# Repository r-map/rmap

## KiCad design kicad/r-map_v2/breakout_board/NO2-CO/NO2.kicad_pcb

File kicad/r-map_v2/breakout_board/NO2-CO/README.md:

Schematic preview
=================

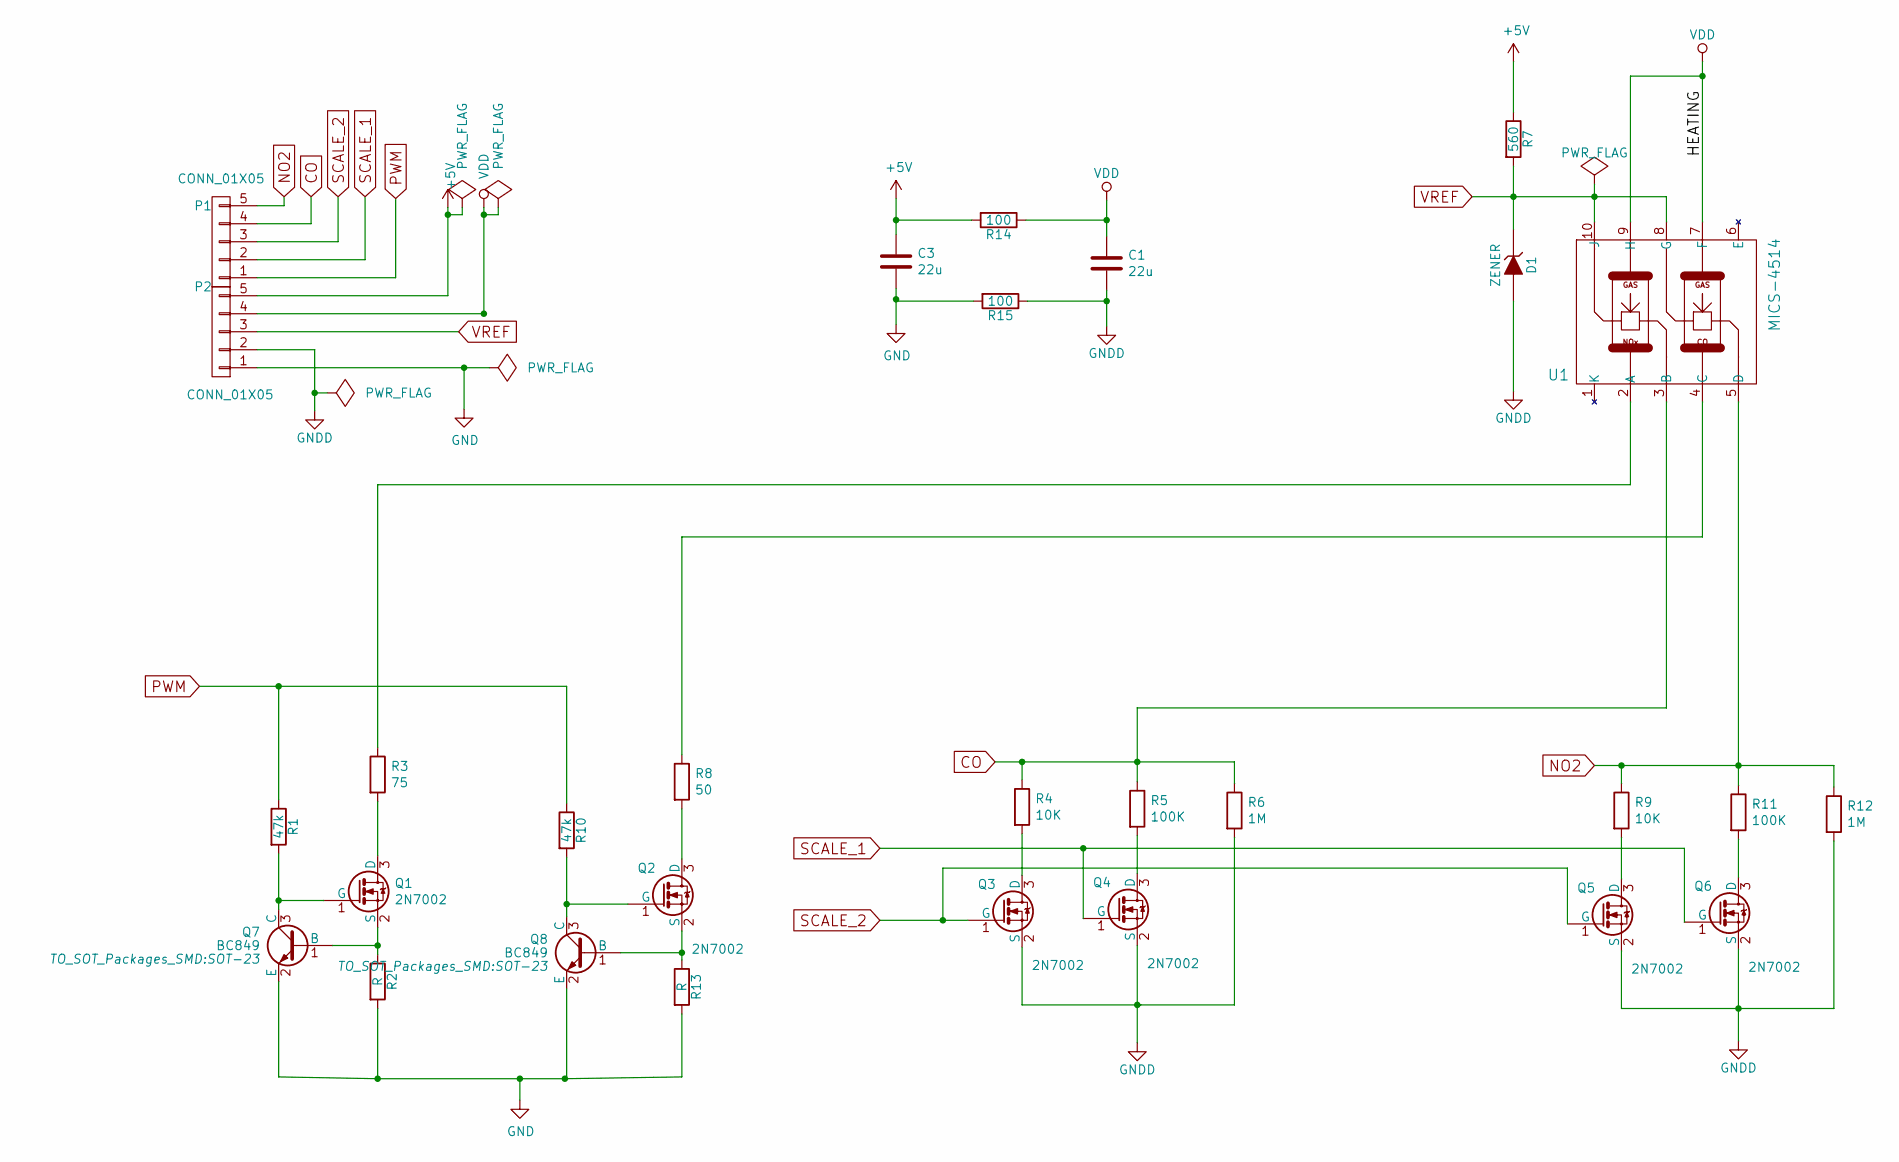
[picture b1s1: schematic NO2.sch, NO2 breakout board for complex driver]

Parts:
C1, C3: 22u; C_0805_HandSoldering
D1: ZENER; SOT-23
P1, P2: CONN_01X05; Pin_Header_Straight_1x05_Pitch2.54mm
Q1, Q2, Q3, Q4, Q5, Q6: 2N7002; SOT-23
Q7, Q8: BC849; SOT-23
R1, R10: 47k; R_0805_HandSoldering
R2, R13: R; R_0805_HandSoldering
R3: 75; R_0805_HandSoldering
R4, R9: 10K; R_0805_HandSoldering
R5, R11: 100K; R_0805_HandSoldering
R6, R12: 1M; R_0805_HandSoldering
R7: 560; R_0805_HandSoldering
R8: 50; R_0805_HandSoldering
R14, R15: 100; R_0805_HandSoldering
U1: MICS-4514

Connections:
+5V: C3.1, P2.5, R7.1, R14.2
CO: P1.4, R4.1, R5.1, R6.1, U1.3 (B)
GND: C3.2, P2.1, Q7.2 (E), Q8.2 (E), R2.2, R13.2, R15.2
GNDD: C1.2, D1.2 (A), P2.2, Q3.2 (S), Q4.2 (S), Q5.2 (S), Q6.2 (S), R6.2, R12.2, R15.1
NO2: P1.5, R9.1, R11.1, R12.1, U1.5 (D)
unnamed: Q1.1 (G), Q7.3 (C), R1.2
unnamed: Q1.2 (S), Q7.1 (B), R2.1
unnamed: Q1.3 (D), R3.2
unnamed: Q2.1 (G), Q8.3 (C), R10.2
unnamed: Q2.2 (S), Q8.1 (B), R13.1
unnamed: Q2.3 (D), R8.2
unnamed: Q3.3 (D), R4.2
unnamed: Q4.3 (D), R5.2
unnamed: Q5.3 (D), R9.2
unnamed: Q6.3 (D), R11.2
unnamed: R3.1, U1.2 (A)
unnamed: R8.1, U1.4 (C)
PWM: P1.1, R1.1, R10.1
SCALE_1: P1.2, Q4.1 (G), Q6.1 (G)
SCALE_2: P1.3, Q3.1 (G), Q5.1 (G)
VDD: C1.1, P2.4, R14.1, U1.7 (F), U1.9 (H)
VREF: D1.1 (K), P2.3, R7.2, U1.8 (G), U1.10 (J)

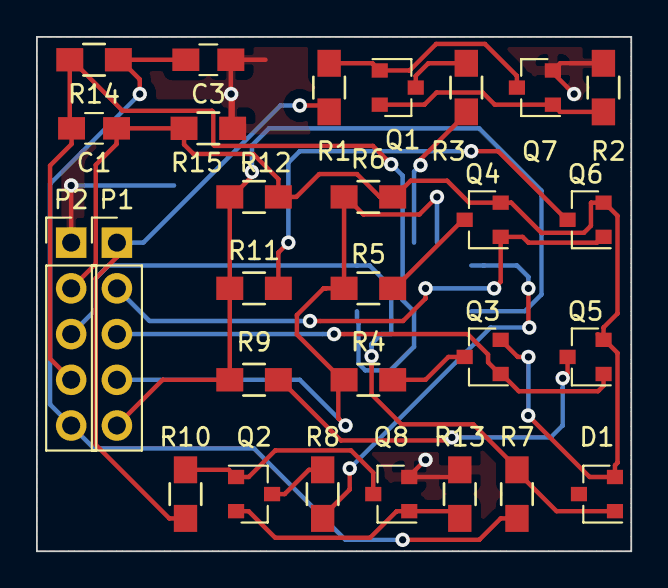
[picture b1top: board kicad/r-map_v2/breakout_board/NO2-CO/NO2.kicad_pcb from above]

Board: 2 copper layers, 33.0 x 28.6 mm, 29 parts (1 on the bottom side), 22 nets.

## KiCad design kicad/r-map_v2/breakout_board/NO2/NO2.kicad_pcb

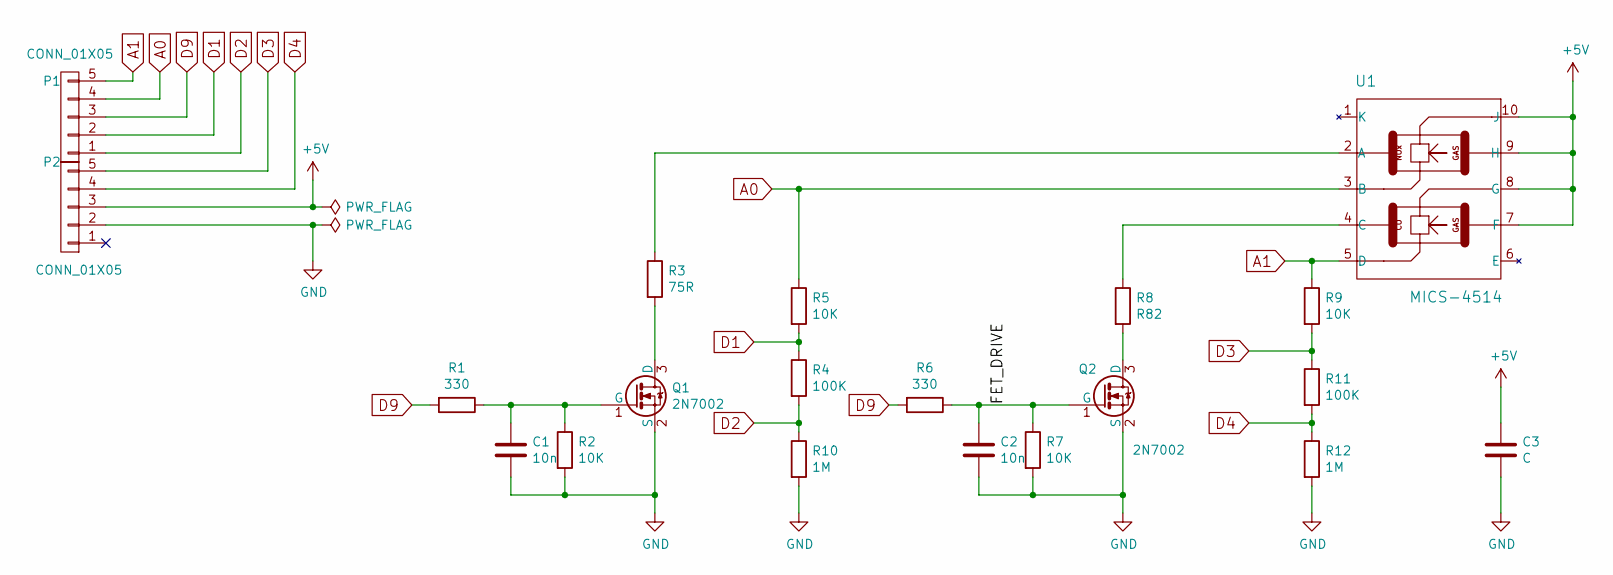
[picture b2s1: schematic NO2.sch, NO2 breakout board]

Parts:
C1, C2: 10n; C_0805_HandSoldering
C3: C
P1, P2: CONN_01X05
Q1, Q2: 2N7002; SOT-23
R1, R6: 330; R_0805
R2, R5, R7, R9: 10K; R_0805
R3: 75R; R_0805
R4, R11: 100K
R8: R82; R_0805
R10, R12: 1M
U1: MICS-4514

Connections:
+5V: C3.1, P2.3, U1.7 (F), U1.8 (G), U1.9 (H), U1.10 (J)
/FET_DRIVE: C2.1, Q2.1 (G), R6.1, R7.1
A0: P1.4, R5.1, U1.3 (B)
A1: P1.5, R9.1, U1.5 (D)
D1: P1.2, R4.1, R5.2
D2: P1.1, R4.2, R10.1
D3: P2.5, R9.2, R11.1
D4: P2.4, R11.2, R12.1
D9: P1.3, R1.2, R6.2
GND: C1.2, C2.2, C3.2, P2.2, Q1.2 (S), Q2.2 (S), R2.2, R7.2, R10.2, R12.2
unnamed: C1.1, Q1.1 (G), R1.1, R2.1
unnamed: Q1.3 (D), R3.2
unnamed: Q2.3 (D), R8.2
unnamed: R3.1, U1.2 (A)
unnamed: R8.1, U1.4 (C)

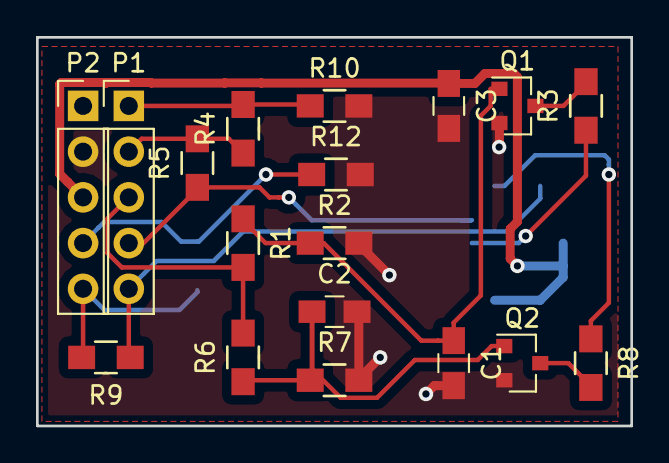
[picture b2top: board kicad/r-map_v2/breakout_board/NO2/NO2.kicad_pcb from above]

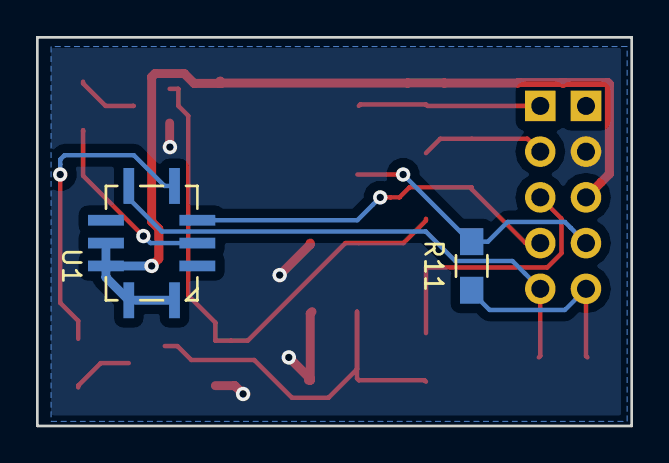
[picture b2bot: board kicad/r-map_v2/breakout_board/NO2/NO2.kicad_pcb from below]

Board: 2 copper layers, 33.0 x 21.6 mm, 20 parts (2 on the bottom side), 15 nets.

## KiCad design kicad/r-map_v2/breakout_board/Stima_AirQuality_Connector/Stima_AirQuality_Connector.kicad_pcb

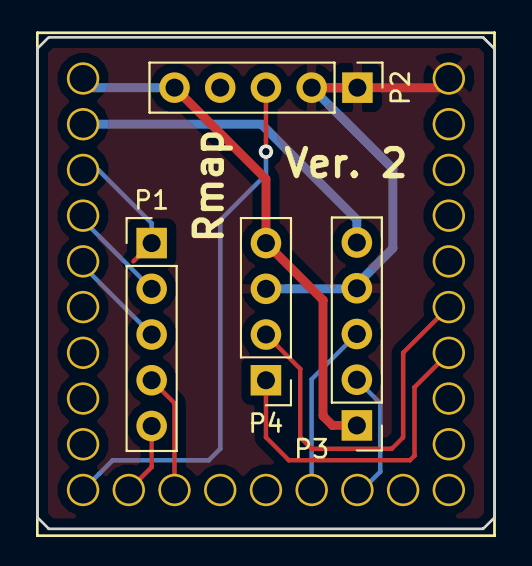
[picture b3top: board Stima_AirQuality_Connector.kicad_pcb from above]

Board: 2 copper layers, 25.4 x 27.3 mm, 5 parts (0 on the bottom side), 13 nets.

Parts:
P1, P2, P3: CONN_01X05; Pin_Header_Straight_1x05_Pitch2.54mm
P4: CONN_01X04; Pin_Header_Straight_1x04_Pitch2.54mm
U1: Microduino; microduino

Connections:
+3V3: P3.5, U1.26
+5V: P2.5, P3.1, P4.4, U1.27
CO: P1.4, U1.16
GND: P2.1, P2.2, P3.4, P4.3, U1.1
NO2: P1.5, U1.17
PWM: P1.1, U1.25
RX: P4.1, U1.7
SCALE_1: P1.2, U1.24
SCALE_2: P1.3, U1.23
SCL: P3.2, U1.12
SDA: P3.3, U1.13
TX: P4.2, U1.6
VREF: P2.3, U1.18

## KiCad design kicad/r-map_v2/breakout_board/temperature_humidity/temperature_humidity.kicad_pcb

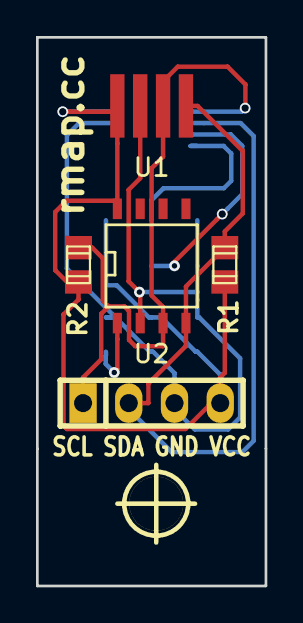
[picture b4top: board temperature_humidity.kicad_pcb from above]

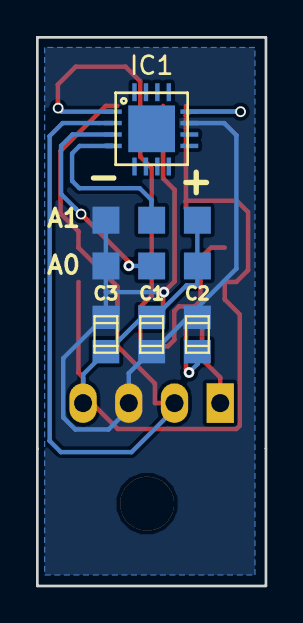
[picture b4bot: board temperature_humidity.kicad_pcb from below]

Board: 2 copper layers, 12.7 x 30.5 mm, 16 parts (8 on the bottom side), 7 nets.

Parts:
3.3V1, 3.3V2: 3.3V; Measurement_Point_Square-SMD-Pad_Small
A1: A1; Measurement_Point_Square-SMD-Pad_Small
C1: 0.22uF; c_0805
C2, C3: 0.1uF; c_0805
GND1, GND3: GND; Measurement_Point_Square-SMD-Pad_Small
IC1: ADT7420; LFCSP_WQ_CP16-17
P3: CONN_01X04; pin_strip_4
P4: A0; Measurement_Point_Square-SMD-Pad_Small
R1, R2: R; r_0805
U1: HIH6100; SIP4_ANGLED
U2: HIH6100-SOIC8; SOIC-8-N
hole_3mm: VAL**; hole_3mm

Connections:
+3.3V: 3.3V1.1, 3.3V2.1, C1.1, C3.1, IC1.12, P3.4, R1.1, R2.1, U1.1, U2.8
/A0: IC1.3, P4.1
/A1: A1.1, IC1.4
GND: C1.2, C2.2, C3.2, GND1.1, GND3.1, IC1.11, P3.3, U1.2, U2.2
unnamed: C2.1, U2.1
SCL: IC1.1, P3.1, R2.2, U1.3, U2.3
SDA: IC1.2, P3.2, R1.2, U1.4, U2.4

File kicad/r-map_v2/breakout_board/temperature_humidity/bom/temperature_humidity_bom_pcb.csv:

Item,Reference(s),Value,Quantity,
1,3.3V1 3.3V2,3.3V,2,Piazzola no componenti
2,A1,A1,1,Piazzola no componenti
3,C1,0.22uF,1,http://it.farnell.com/multicomp/mc0805b224m250ct/ceramic-cap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
4,C2 C3,0.1uF,3,http://it.farnell.com/avx/08053e104zat2a/ceramic-capacitor-0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
5,GND1 GND3,GND,2,Piazzola no componenti
6,IC1,ADT7420,1,http://it.farnell.com/analog-devices/adt7420ucpz-r2/temp-sen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
7,P3,CONN_01X04,1,http://it.farnell.com/multicomp/2211s-04g/connettore-header-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
8,P4,A0,1,Piazzola no componenti
9,U1,HIH6100,1,Honeywell HIH6100
10,U2,HIH6100-SOIC8,1,Honeywell HIH6100-SOIC8

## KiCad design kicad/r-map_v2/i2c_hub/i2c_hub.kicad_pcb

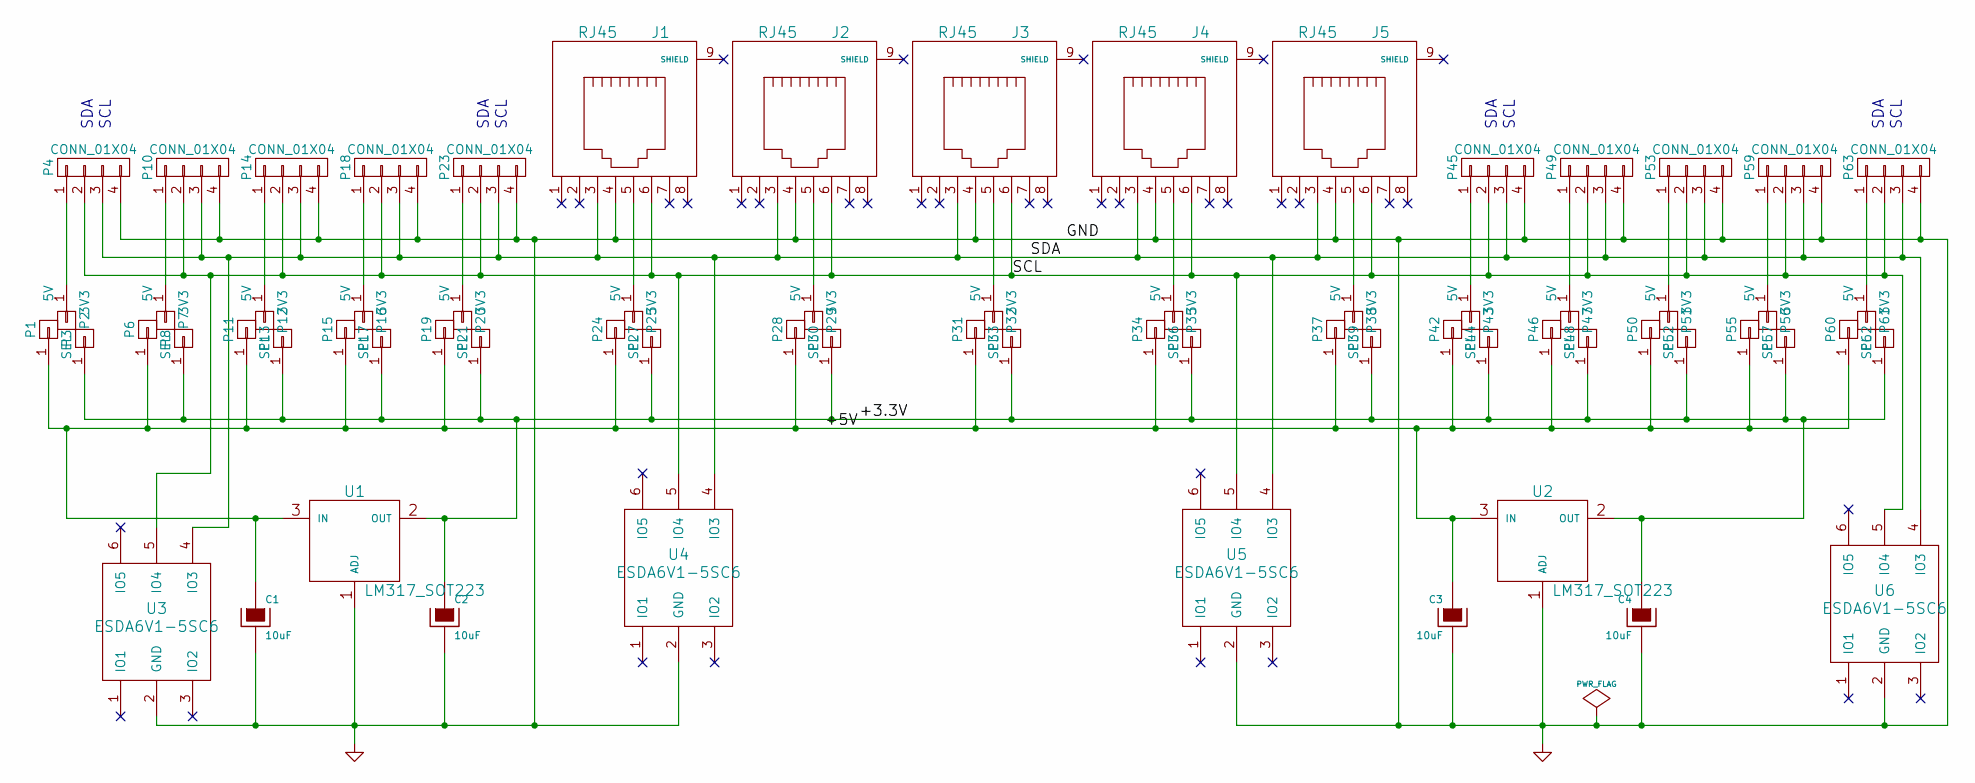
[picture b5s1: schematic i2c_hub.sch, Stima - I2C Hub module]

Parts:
C1, C2, C3, C4: 10uF; c_1206
J1, J2, J3, J4, J5: RJ45; RJ45_8
P1, P6, P11, P15, P19, P24, P28, P31, P34, P37, P42, P46, P50, P55, P60: 5V; Measurement_Point_Round-SMD-Pad_Small
P2, P7, P12, P16, P20, P25, P29, P32, P35, P38, P43, P47, P51, P56, P61: SEL; Measurement_Point_Round-SMD-Pad_Small
P3, P8, P13, P17, P21, P27, P30, P33, P36, P39, P44, P48, P52, P57, P62: 3V3; Measurement_Point_Round-SMD-Pad_Small
P4, P10, P14, P18, P23, P45, P49, P53, P59, P63: CONN_01X04; pin_strip_4
U1, U2: LM317_SOT223; sot223
U3, U4, U5, U6: ESDA6V1-5SC6; sot23-6

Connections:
/+3.3V: C2.1, C4.1, P3.1, P8.1, P13.1, P17.1, P21.1, P27.1, P30.1, P33.1, P36.1, P39.1, P44.1, P48.1, P52.1, P57.1, P62.1, U1.2 (OUT), U2.2 (OUT), U3.1 (IO1), U5.1 (IO1), U6.1 (IO1)
/+5V: C1.1, C3.1, P1.1, P6.1, P11.1, P15.1, P19.1, P24.1, P28.1, P31.1, P34.1, P37.1, P42.1, P46.1, P50.1, P55.1, P60.1, U1.3 (IN), U2.3 (IN), U3.6 (IO5), U4.1 (IO1), U4.6 (IO5), U5.6 (IO5), U6.6 (IO5)
/SCL: J1.6, J2.6, J3.6, J4.6, J5.6, P4.2, P10.2, P14.2, P18.2, P23.2, P45.2, P49.2, P53.2, P59.2, P63.2, U3.5 (IO4), U4.5 (IO4), U5.5 (IO4), U6.5 (IO4)
/SDA: J1.3, J2.3, J3.3, J4.3, J5.3, P4.3, P10.3, P14.3, P18.3, P23.3, P45.3, P49.3, P53.3, P59.3, P63.3, U3.4 (IO3), U4.4 (IO3), U5.4 (IO3), U6.4 (IO3)
GND: C1.2, C2.2, C3.2, C4.2, J1.4, J2.4, J3.4, J4.4, J5.4, P4.4, P10.4, P14.4, P18.4, P23.4, P45.4, P49.4, P53.4, P59.4, P63.4, U1.1 (ADJ), U2.1 (ADJ), U3.2 (GND), U4.2 (GND), U5.2 (GND), U6.2 (GND)
unnamed: J1.5, P25.1
unnamed: J2.5, P29.1
unnamed: J3.5, P32.1
unnamed: J4.5, P35.1
unnamed: J5.5, P38.1
unnamed: P2.1, P4.1
unnamed: P7.1, P10.1
unnamed: P12.1, P14.1
unnamed: P16.1, P18.1
unnamed: P20.1, P23.1
unnamed: P43.1, P45.1
unnamed: P47.1, P49.1
unnamed: P51.1, P53.1
unnamed: P56.1, P59.1
unnamed: P61.1, P63.1

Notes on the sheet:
SDA
SCL

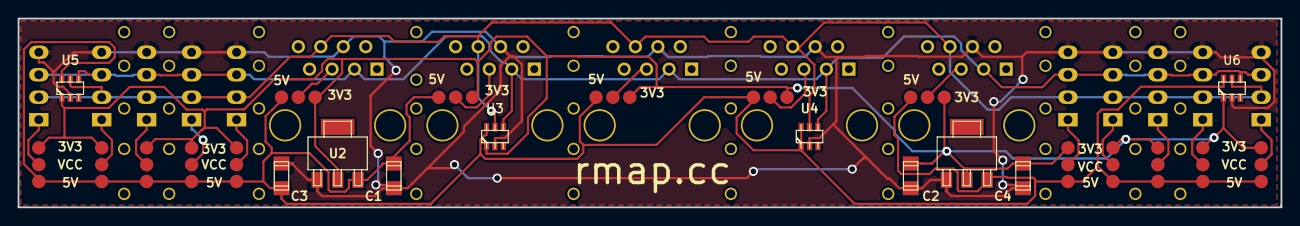
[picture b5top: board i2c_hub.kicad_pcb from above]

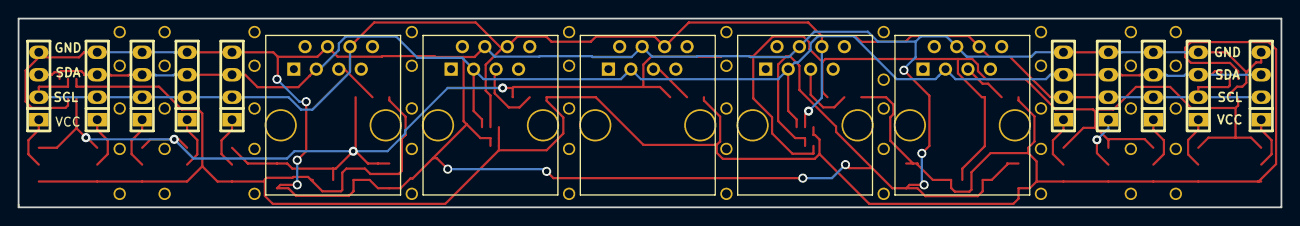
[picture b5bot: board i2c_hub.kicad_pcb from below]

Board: 2 copper layers, 142.7 x 21.3 mm, 70 parts (15 on the bottom side), 20 nets.

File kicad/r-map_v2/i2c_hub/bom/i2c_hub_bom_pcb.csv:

Item,Reference(s),Value,Quantity,Package,Esempio
1,C1 C2 C3 C4,10uF,4,1206 smd,http://it.farnell.com/kemet/c1206c106k4pactu/condensatore-ml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
2,J1 J2 J3 J4 J5,RJ45,5,connettore RJ45 non schermato, http://it.farnell.com/fci/54601-908wplf/modulare-jack-tht-r-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
3,P1 P11 P15 P19 P24 P28 P31 P34 P37 P42 P46 P50 P55 P6 P60,5V,15,piazzola senza componenti,
4,P10 P14 P18 P23 P4 P45 P49 P53 P59 P63,CONN_01X04,10,strip connector maschio 4 pin,
5,P12 P16 P2 P20 P25 P29 P32 P35 P38 P43 P47 P51 P56 P61 P7,SEL,15,piazzola senza componenti,
6,P13 P17 P21 P27 P3 P30 P33 P36 P39 P44 P48 P52 P57 P62 P8,3V3,15,piazzola senza componenti,
7,U1 U2,LM1117-3.3,2,SOT-223 smd,http://it.farnell.com/texas-instruments/lm1117mp-3-3/v-reg-l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
8,U3 U4 U5 U6,ESDA6V1-5SC6,4,SOT23-6 smd,http://it.farnell.com/stmicroelectronics/esda6v1-5sc6/transi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

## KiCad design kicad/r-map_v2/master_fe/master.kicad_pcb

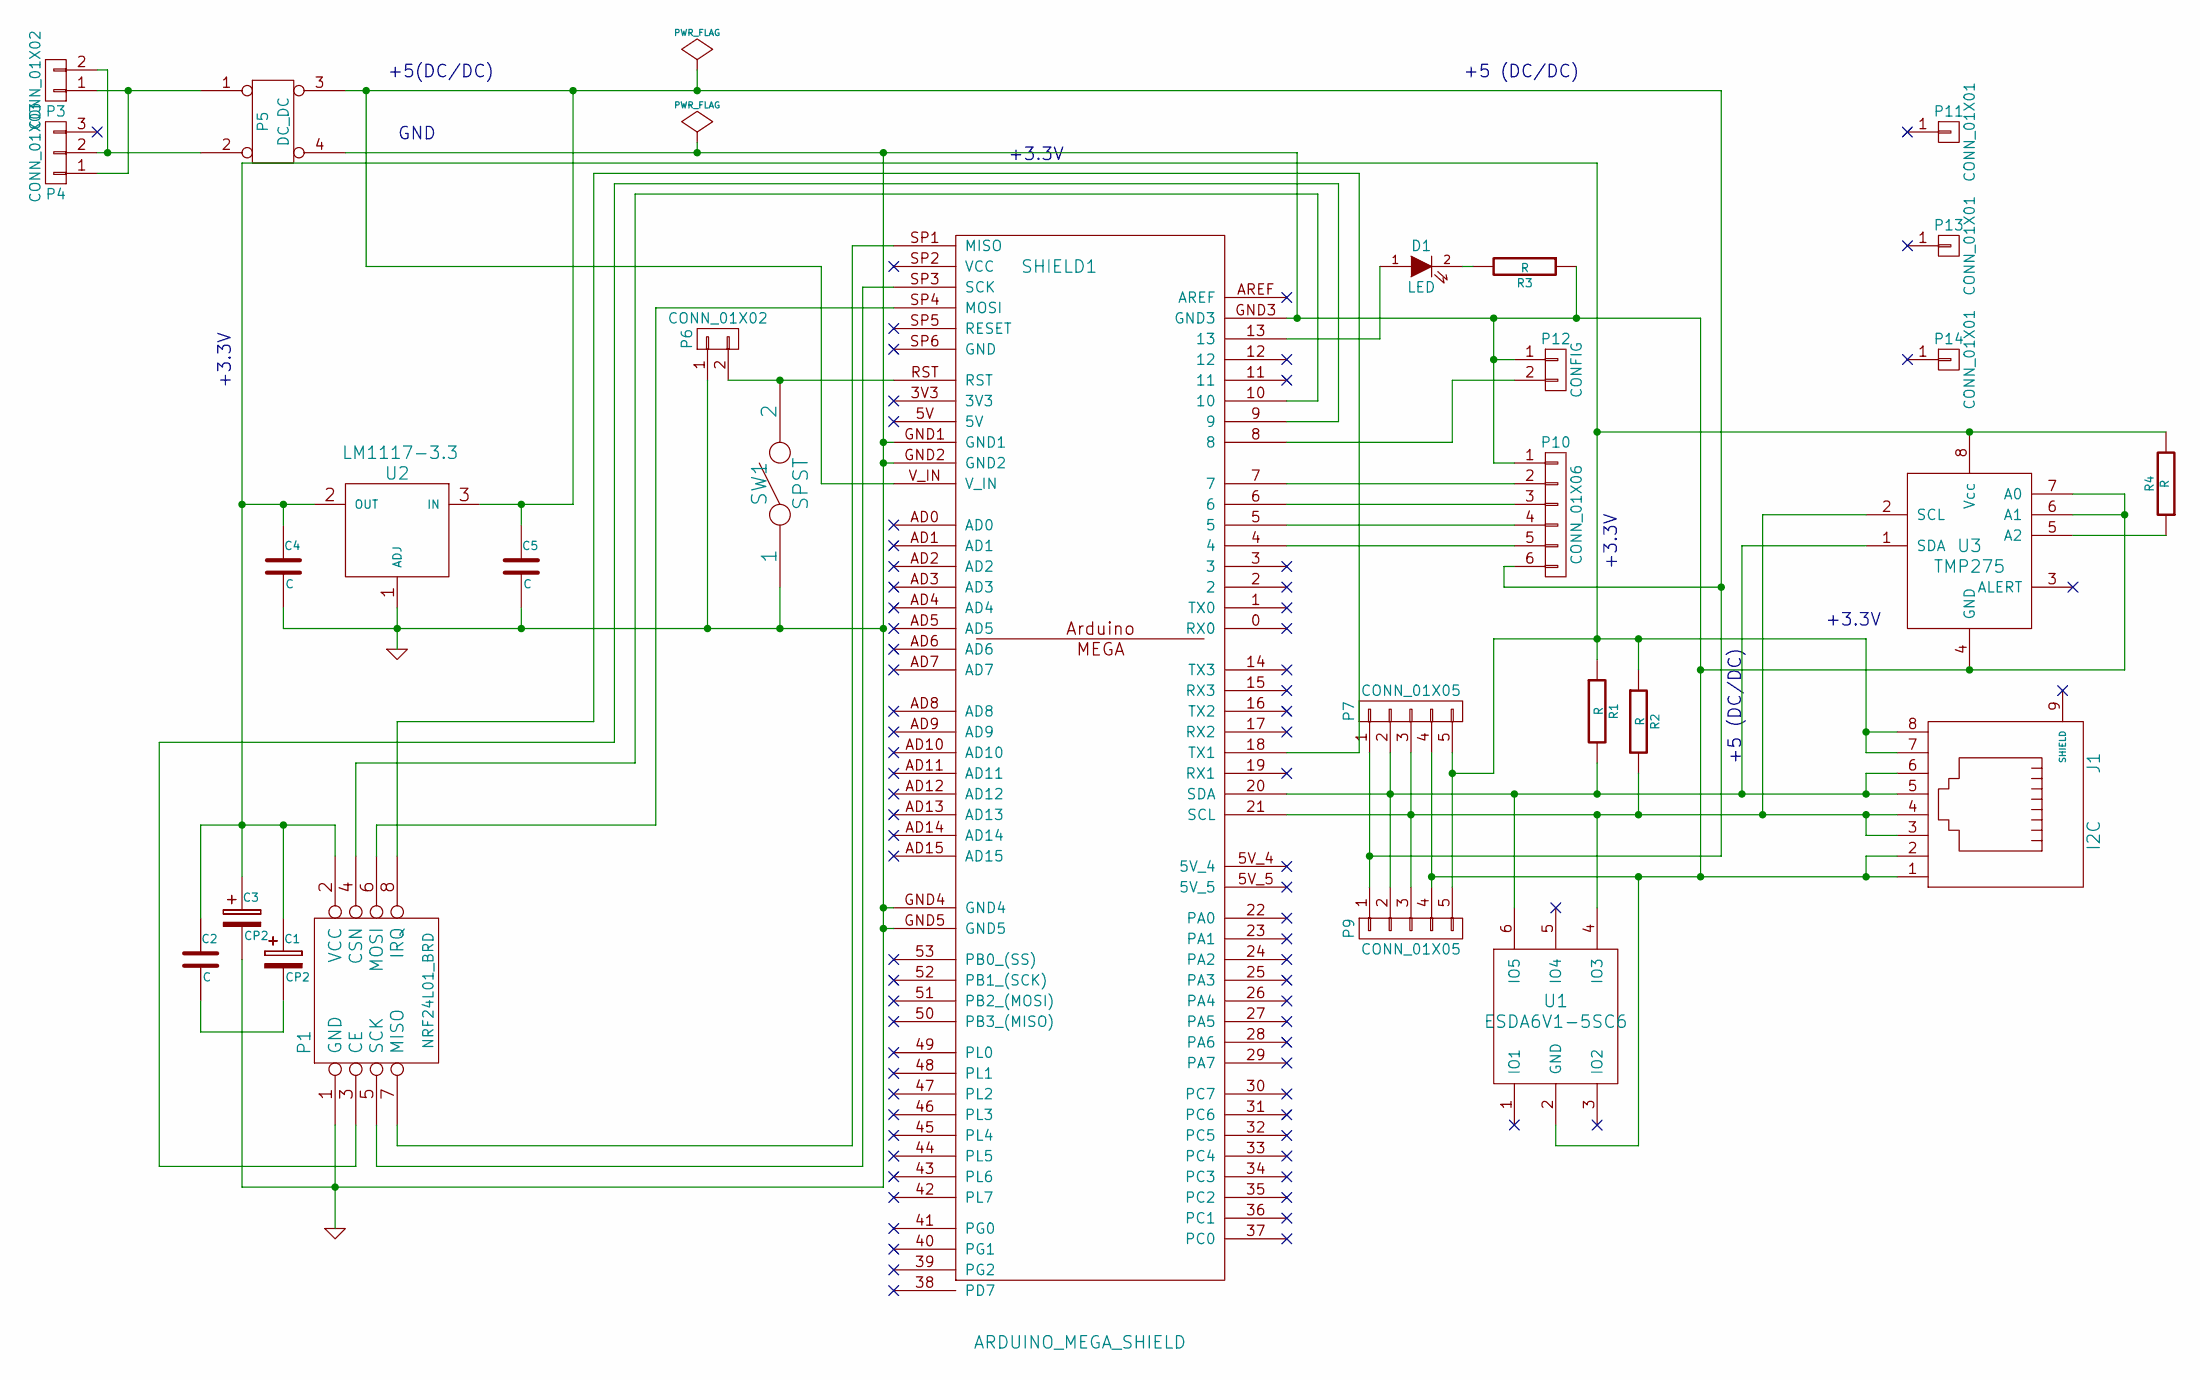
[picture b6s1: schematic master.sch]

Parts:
C1: CP2; SMD-1206
C2, C4, C5: C; SMD-1206
C3: CP2; C1.5V8V
D1: LED; LED-3MM
J1: I2C; RJ45_8
P1: NRF24L01_BRD; NRF24L01
P3, P6: CONN_01X02; Pin_Header_Straight_1x02
P4: CONN_01X03; BARREL_JACK
P5: DC_DC
P7, P9: CONN_01X05; Pin_Header_Straight_1x05
P10: CONN_01X06; Pin_Header_Straight_1x06
P11, P13, P14: CONN_01X01; MountingHole_3mm
P12: CONFIG; Pin_Header_Straight_1x02
R1, R2, R3, R4: R; R3-LARGE_PADS
SHIELD1: ARDUINO_MEGA_SHIELD
SW1: SPST; SW_PUSH_SMALL
U1: ESDA6V1-5SC6; SOT-23-6
U2: LM1117-3.3; SOT-223
U3: TMP275; SO-8

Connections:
GND: C3.2, C4.2, C5.2, J1.1, J1.2, P1.1 (GND), P5.4, P6.1, P7.4, P9.4, P10.1, P12.1, R3.1, SHIELD1.GND1, SHIELD1.GND2, SHIELD1.GND3, SHIELD1.GND4, SHIELD1.GND5, SW1.1, U1.2 (GND), U2.1 (ADJ), U3.4 (GND), U3.6 (A1), U3.7 (A0)
unnamed: C1.1, C2.1, C3.1, C4.1, J1.7, J1.8, P1.2 (VCC), P7.5, P9.5, R1.1, R2.1, R4.2, U2.2 (OUT), U3.8 (Vcc)
unnamed: C1.2, C2.2
unnamed: C5.1, P5.3, P7.1, P9.1, P10.6, SHIELD1.V_IN, U2.3 (IN)
unnamed: D1.1 (A), SHIELD1.13
unnamed: D1.2 (K), R3.2
unnamed: J1.3, J1.4, P7.3, P9.3, R2.2, SHIELD1.21 (SCL), U1.4 (IO3), U3.2 (SCL)
unnamed: J1.5, J1.6, P7.2, P9.2, R1.2, SHIELD1.20 (SDA), U1.6 (IO5), U3.1 (SDA)
unnamed: P1.3 (CE), SHIELD1.9
unnamed: P1.4 (CSN), SHIELD1.10
unnamed: P1.5 (SCK), SHIELD1.SP3 (SCK)
unnamed: P1.6 (MOSI), SHIELD1.SP4 (MOSI)
unnamed: P1.7 (MISO), SHIELD1.SP1 (MISO)
unnamed: P1.8 (IRQ), SHIELD1.18 (TX1)
unnamed: P3.1, P4.1, P5.1
unnamed: P3.2, P4.2, P5.2
unnamed: P6.2, SHIELD1.RST, SW1.2
unnamed: P10.2, SHIELD1.7
unnamed: P10.3, SHIELD1.6
unnamed: P10.4, SHIELD1.5
unnamed: P10.5, SHIELD1.4
unnamed: P12.2, SHIELD1.8
unnamed: R4.1, U3.5 (A2)

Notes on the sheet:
+5 (DC/DC)
GND
+5(DC/DC)
+3.3V

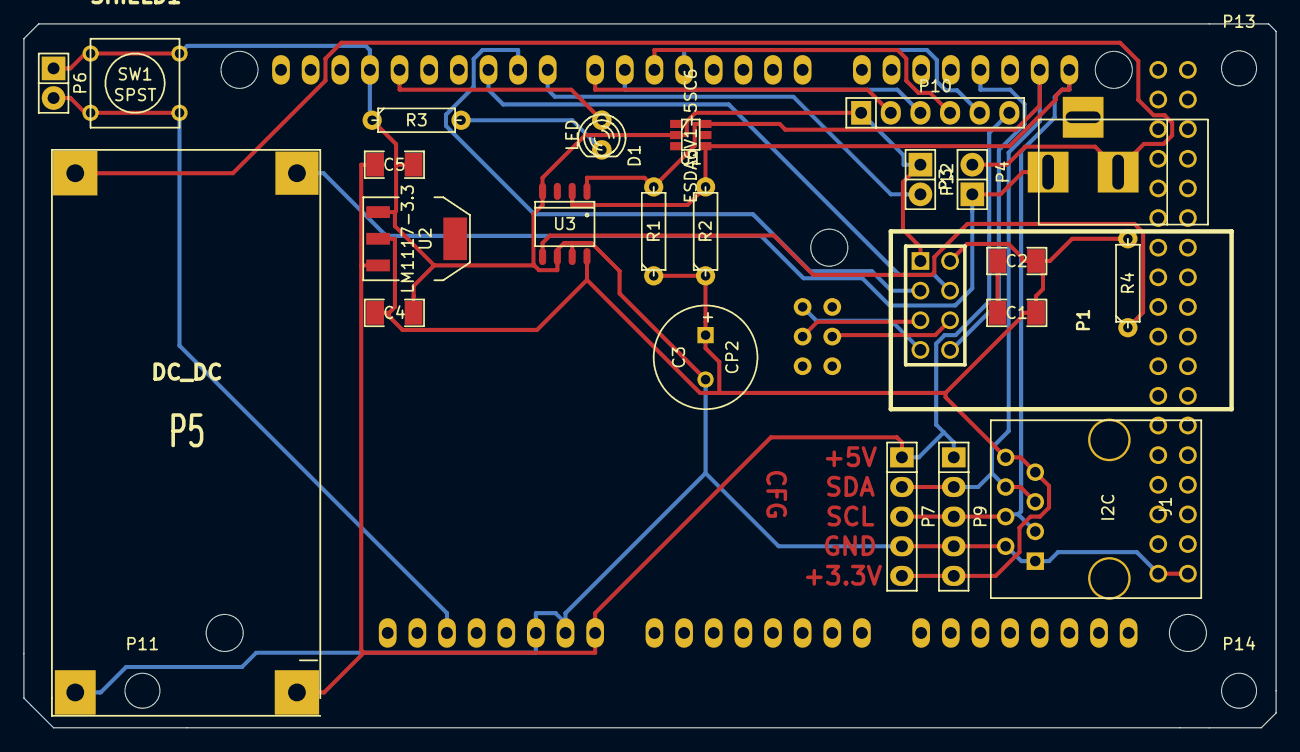
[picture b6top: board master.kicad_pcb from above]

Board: 2 copper layers, 107.3 x 60.3 mm, 28 parts (0 on the bottom side), 23 nets.

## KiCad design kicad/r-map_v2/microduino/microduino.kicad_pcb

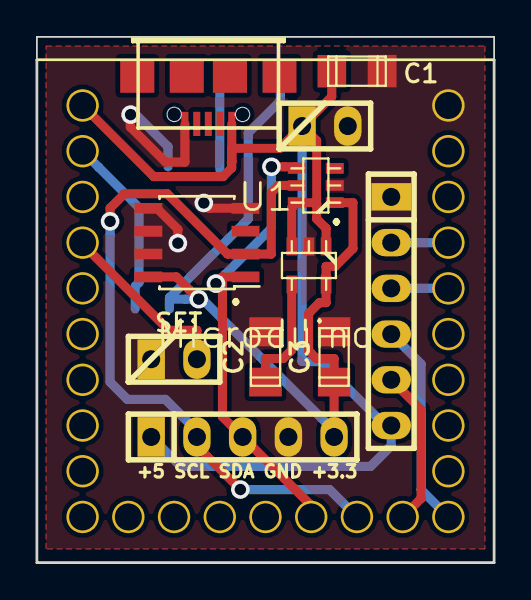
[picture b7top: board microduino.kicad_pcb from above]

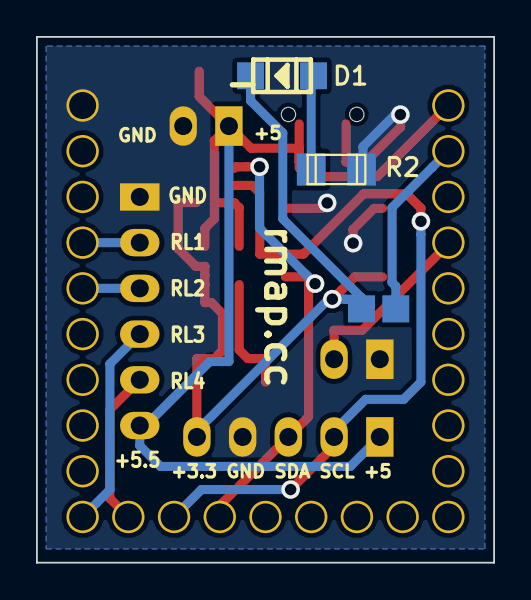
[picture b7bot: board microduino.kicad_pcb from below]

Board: 2 copper layers, 25.4 x 29.2 mm, 16 parts (4 on the bottom side), 13 nets.

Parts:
C1: 1uF; c_1206
C2: 0.01uF; c_1206
C3: 2.2uF; c_1206
D1: LED_SMD; Led_1206
P1: CONN_01X02; pin_strip_2
P2: CONN_RELE_BOARD; pin_strip_6
P3: CONN_01X05; pin_strip_5
P4: CONFIG; pin_strip_2
P5: USB_OTG; conn_usb_B_micro_smd-2
P6, P7: CONN_01X01; Measurement_Point_Square-SMD-Pad_Small
R2: 820; r_1206
U1: Microduino; microduino
U2: ESDA6V1-5SC6; sot23-6
U3: REG113NA-3.3/250; sot23-5
U4: TMP275; SOIC-8_3.9x4.9mm_Pitch1.27mm

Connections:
/+3.3V: C3.1, D1.2, P3.5, P7.1, U2.1, U3.5, U4.8
/+5V: C1.1, P1.1, P2.6, P3.1, P5.1, U1.27, U2.6, U3.1, U3.3
/SCL: P3.2, U1.12, U2.5, U4.2
/SDA: P3.3, U1.13, U2.4, U4.1
GND: C1.2, C2.2, C3.2, P1.2, P2.1, P3.4, P4.1, P5.5, R2.2, U1.1, U2.2, U3.2, U4.4, U4.5, U4.6, U4.7
unnamed: C2.1, U3.4
unnamed: D1.1, R2.1
unnamed: P2.2, U1.4
unnamed: P2.3, U1.5
unnamed: P2.4, U1.10
unnamed: P2.5, U1.11
unnamed: P4.2, U1.24
unnamed: P6.1, U1.26

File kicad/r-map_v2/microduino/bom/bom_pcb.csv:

Item,Reference(s),Value,Quantity
1,C1,1uF,1
2,C2,0.01uF,1
3,C3,2.2uF,1
4,D1,LED_SMD,1
5,P1,CONN_01X02,1
6,P2,CONN_RELE_BOARD,1
7,P3,CONN_01X05,1
8,P4,CONFIG,1
9,P5,USB_OTG,1
10,P6 P7,CONN_01X01,2
11,R2,150,1
12,U1,Microduino,1
13,U2,ESDA6V1-5SC6,1
14,U3,LP2985LV,1
15,U4,TMP275,1

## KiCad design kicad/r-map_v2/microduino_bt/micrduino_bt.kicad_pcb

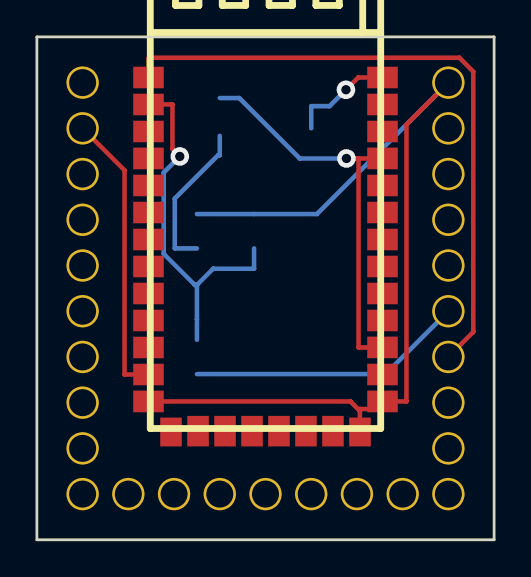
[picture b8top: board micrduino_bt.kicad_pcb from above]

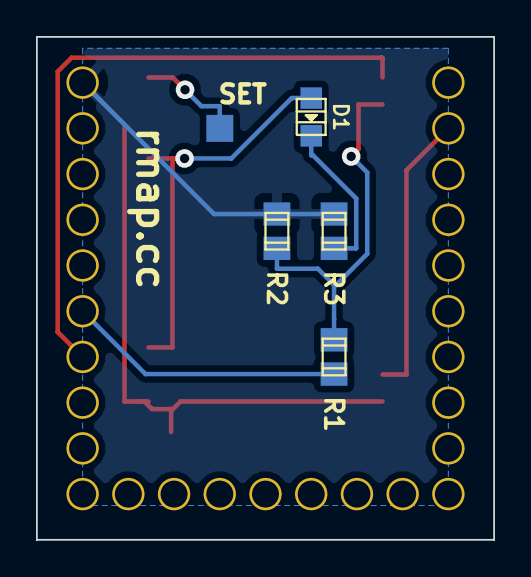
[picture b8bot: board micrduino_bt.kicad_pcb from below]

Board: 2 copper layers, 25.4 x 27.9 mm, 7 parts (4 on the bottom side), 8 nets.

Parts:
D1: LED; Led_0805
P3: CONN_01X01; Measurement_Point_Square-SMD-Pad_Small
R1: 8K2; r_0805
R2: 15K; r_0805
R3: R; r_0805
U1: Microduino; microduino
U2: ITEAD_HC-05; HC-05

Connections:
/INT_28J60: R1.1, U1.6
/LED: D1.1, U2.24, U2.31
/RX1: U1.7, U2.1
/SET: P3.1, U2.34
GND: R2.2, R3.2, U1.1, U2.13, U2.21, U2.22
unnamed: D1.2, R3.1
unnamed: R1.2, R2.1, U2.2
unnamed: U1.26, U2.12

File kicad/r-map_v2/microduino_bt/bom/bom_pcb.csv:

Item,Reference(s),Value,Quantity,Riferimento,Valore ,Package,Esempio
1,D1,LED,1,D,LED,LED in package 0805,
2,P1 P2 P3 P4 P5 P6,CONN_01X01,6,P,CONN_01X01,"pad da saldare, non componenti",
3,R1,8K2,1,,8K2,package 0805,
4,R2,15K,1,,15K,package 0805,
5,R3,150,1,R,150,package 0805,
6,R4,10K,1,,10K,package 0805,
7,U1,Microduino,1,,,connettori strip pin torniti femmina 3 x 9 contatti,
8,U2,ITEAD_HC-05,1,,,modulo HC-06,http://www.wavesen.com/probig.asp?id=24

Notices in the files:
kicad/r-map_v2/breakout_board/temperature_humidity/temperature_humidity.kicad_pcb:
Released under MIT License(MIT)
